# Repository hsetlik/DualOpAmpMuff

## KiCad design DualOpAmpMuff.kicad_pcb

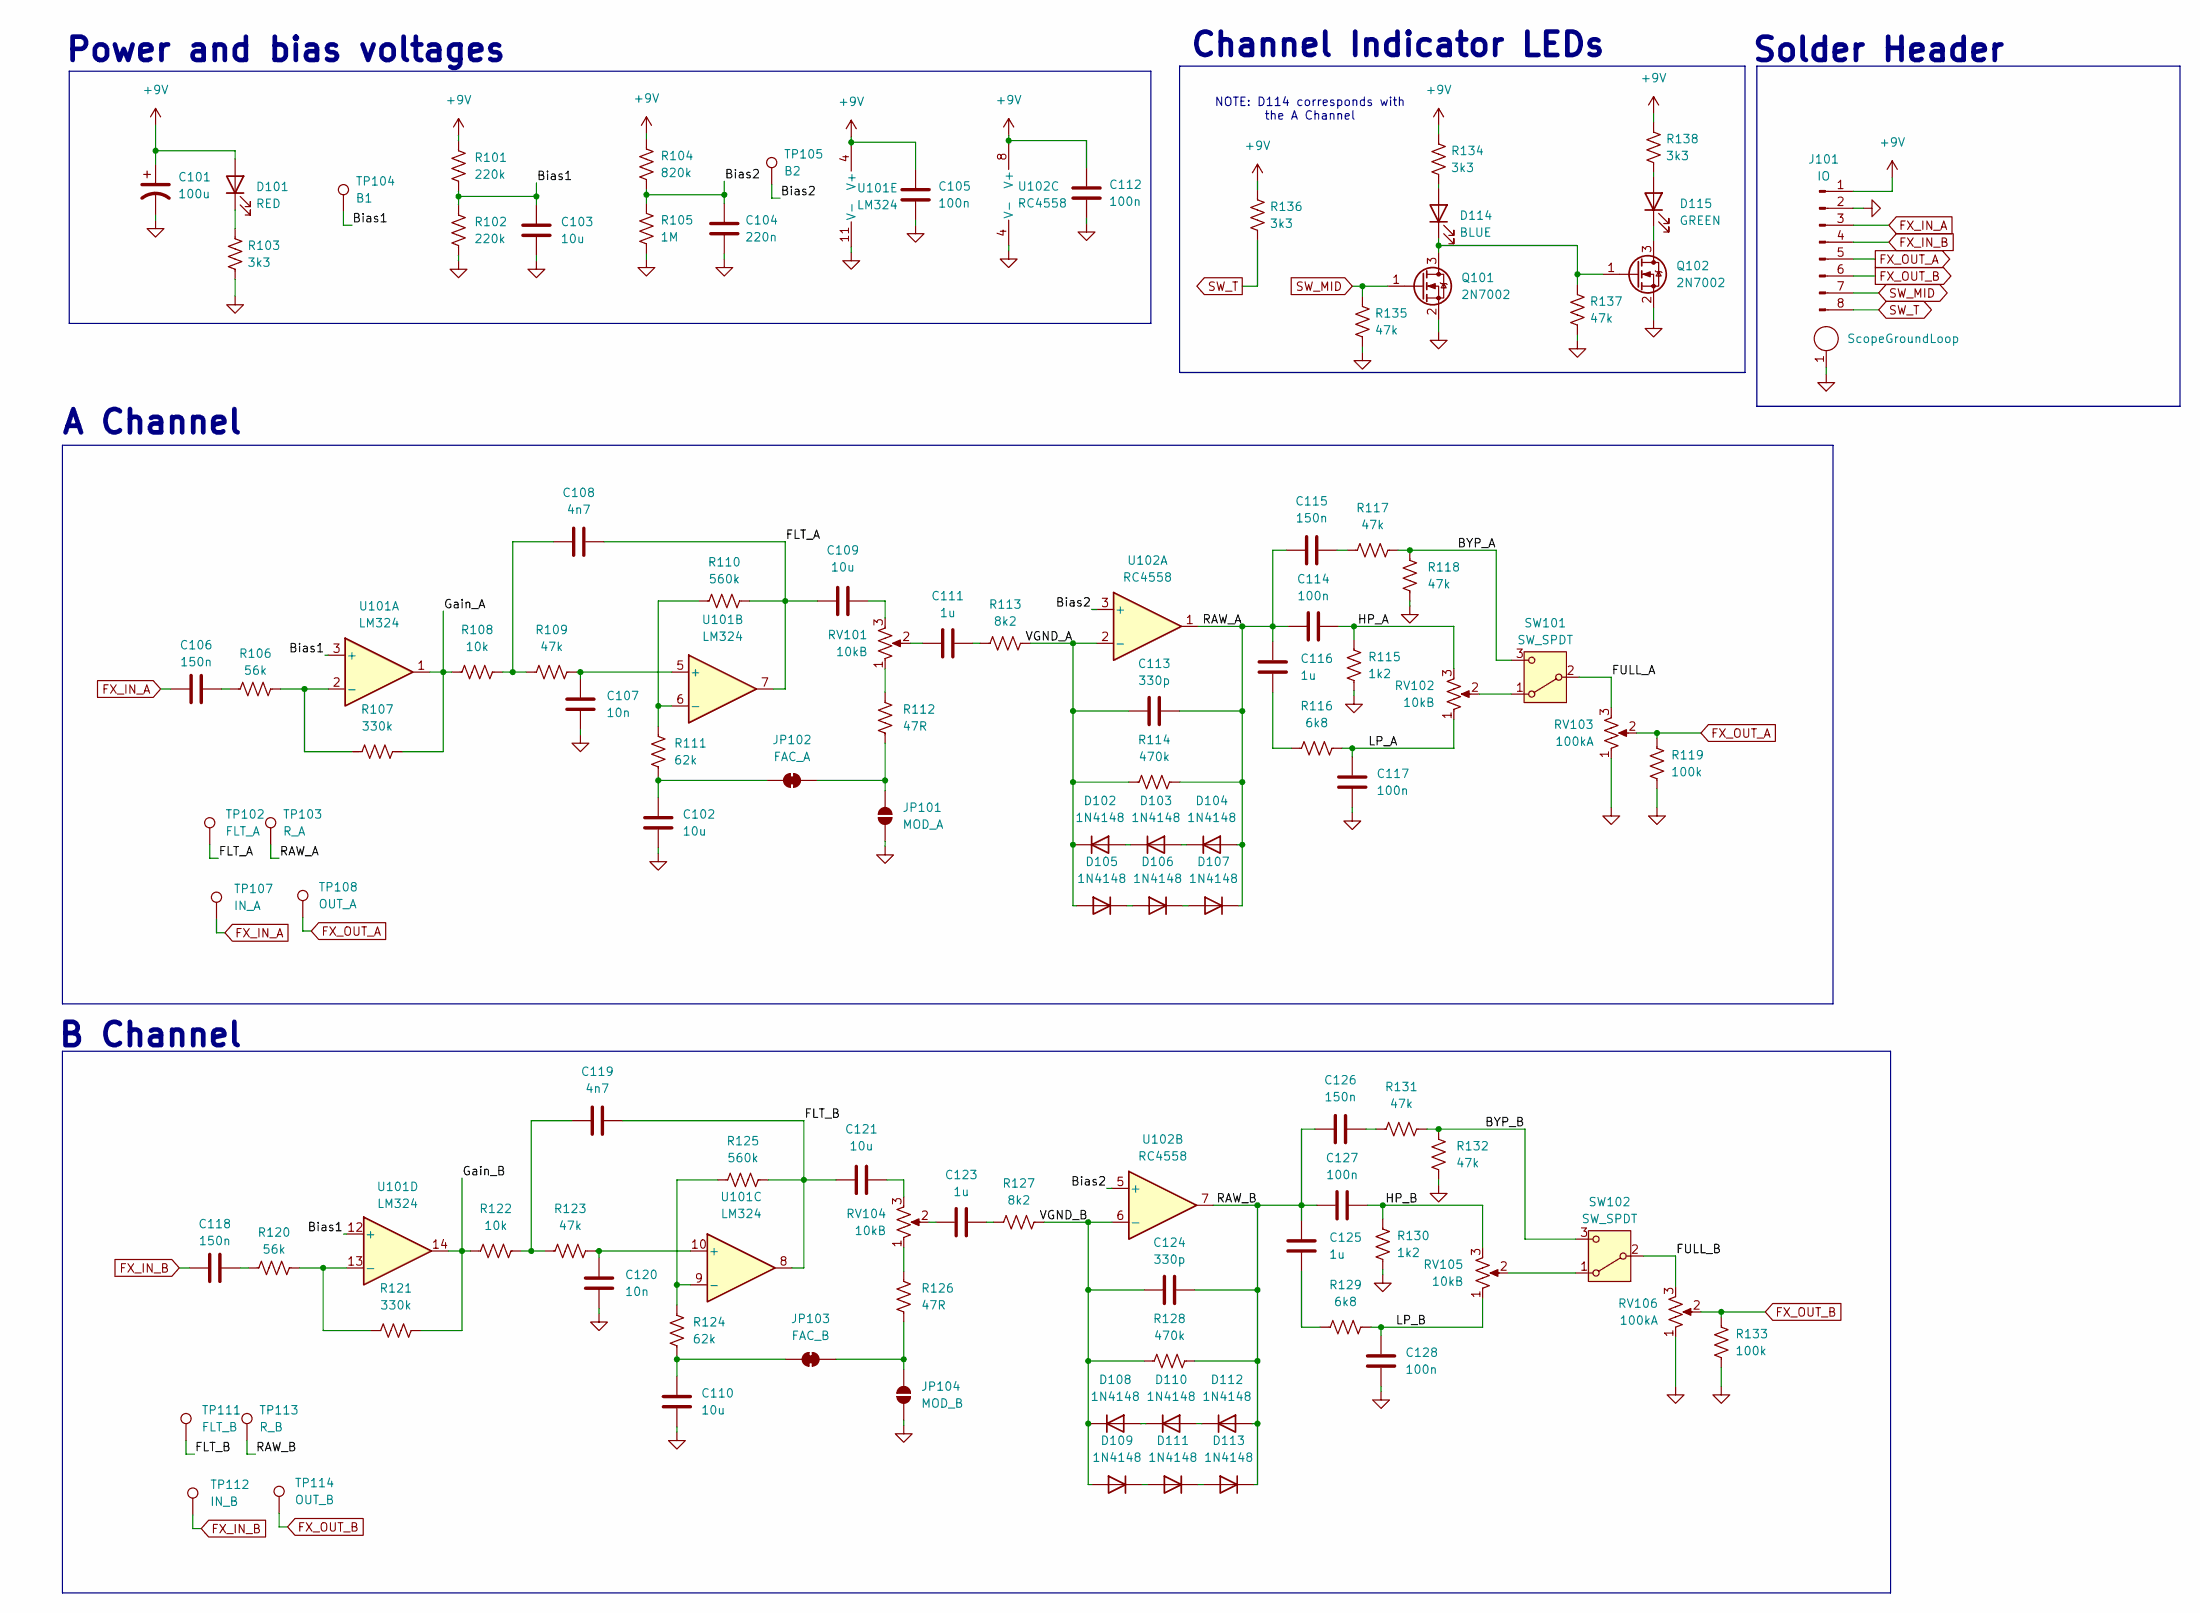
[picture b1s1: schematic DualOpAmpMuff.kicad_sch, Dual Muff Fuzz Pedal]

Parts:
C101: 100u; CP_Radial_D6.3mm_P2.50mm
C102, C103, C109, C110, C121: 10u; C_0805_2012Metric
C104: 220n; C_0805_2012Metric
C105, C112, C114, C117, C127, C128: 100n; C_0805_2012Metric
C106, C115, C118, C126: 150n; C_0805_2012Metric
C107, C120: 10n; C_0805_2012Metric
C108, C119: 4n7; C_0805_2012Metric
C111, C116, C123, C125: 1u; C_0805_2012Metric
C113, C124: 330p; C_0805_2012Metric
D101: RED; LED_D3.0mm
D102, D103, D104, D105, D106, D107, D108, D109, D110, D111, D112, D113: 1N4148; D_SOD-123
D114: BLUE; LED_D3.0mm
D115: GREEN; LED_D3.0mm
J101: IO; PinHeader_1x08_P2.54mm_Vertical
J102: ScopeGroundLoop; THT_GND_WIRE
JP101: MOD_A; SolderJumper-2_P1.3mm_Open_Pad1.0x1.5mm
JP102: FAC_A; SolderJumper-2_P1.3mm_Bridged_Pad1.0x1.5mm
JP103: FAC_B; SolderJumper-2_P1.3mm_Bridged_Pad1.0x1.5mm
JP104: MOD_B; SolderJumper-2_P1.3mm_Open_Pad1.0x1.5mm
Q101, Q102: 2N7002; SOT-23
R101, R102: 220k; R_0805_2012Metric
R103, R134, R136, R138: 3k3; R_0805_2012Metric
R104: 820k; R_0805_2012Metric
R105: 1M; R_0805_2012Metric
R106, R120: 56k; R_0805_2012Metric
R107, R121: 330k; R_0805_2012Metric
R108, R122: 10k; R_0805_2012Metric
R109, R117, R118, R123, R131, R132, R135, R137: 47k; R_0805_2012Metric
R110, R125: 560k; R_0805_2012Metric
R111, R124: 62k; R_0805_2012Metric
R112, R126: 47R; R_0805_2012Metric
R113, R127: 8k2; R_0805_2012Metric
R114, R128: 470k; R_0805_2012Metric
R115, R130: 1k2; R_0805_2012Metric
R116, R129: 6k8; R_0805_2012Metric
R119, R133: 100k; R_0805_2012Metric
RV101, RV102, RV104, RV105: 10kB; Potentiometer_Alpha_RD901F-40-00D_Single_Vertical_CircularH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
RV103, RV106: 100kA; Potentiometer_Alpha_RD901F-40-00D_Single_Vertical_CircularH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
SW101, SW102: SW_SPDT; Switch_Toggle_SPDT_Mini_SolderLug
TP102: FLT_A; TestPoint_THTPad_D2.0mm_Drill1.0mm_VAL
TP103: R_A; TestPoint_THTPad_D2.0mm_Drill1.0mm_VAL
TP104: B1; TestPoint_THTPad_D2.0mm_Drill1.0mm_VAL
TP105: B2; TestPoint_THTPad_D2.0mm_Drill1.0mm_VAL
TP107: IN_A; TestPoint_THTPad_D2.0mm_Drill1.0mm_VAL
TP108: OUT_A; TestPoint_THTPad_D2.0mm_Drill1.0mm_VAL
TP111: FLT_B; TestPoint_THTPad_D2.0mm_Drill1.0mm_VAL
TP112: IN_B; TestPoint_THTPad_D2.0mm_Drill1.0mm_VAL
TP113: R_B; TestPoint_THTPad_D2.0mm_Drill1.0mm_VAL
TP114: OUT_B; TestPoint_THTPad_D2.0mm_Drill1.0mm_VAL
U101: LM324; DIP-14_W7.62mm
U102: RC4558; DIP-8_W7.62mm

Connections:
+9V: C101.1, C105.1, C112.1, D101.2 (A), J101.1, R101.2, R104.2, R134.2, R136.2, R138.2, U101.4 (V+), U102.8 (V+)
/BYP_A: R117.2, R118.1, SW101.3 (C)
/BYP_B: R131.2, R132.1, SW102.3 (C)
/Bias1: C103.1, R101.1, R102.2, TP104.1, U101.3 (+), U101.12 (+)
/Bias2: C104.1, R104.1, R105.2, TP105.1, U102.3 (+), U102.5 (+)
/FLT_A: C108.2, C109.2, R110.2, TP102.1, U101.7
/FLT_B: C119.2, C121.1, R125.2, TP111.1, U101.8
/FULL_A: RV103.3, SW101.2 (B)
/FULL_B: RV106.3, SW102.2 (B)
/Gain_A: R107.2, R108.1, U101.1
/Gain_B: R121.2, R122.1, U101.14
/HP_A: C114.2, R115.1, RV102.3
/HP_B: C127.2, R130.1, RV105.3
/LP_A: C117.1, R116.2, RV102.1
/LP_B: C128.1, R129.2, RV105.1
/RAW_A: C113.2, C114.1, C115.1, C116.1, D104.2 (A), D107.1 (K), R114.2, TP103.1, U102.1
/RAW_B: C124.2, C125.1, C126.1, C127.1, D112.2 (A), D113.1 (K), R128.2, TP113.1, U102.7
/VGND_A: C113.1, D102.1 (K), D105.2 (A), R113.2, R114.1, U102.2 (-)
/VGND_B: C124.1, D108.1 (K), D109.2 (A), R127.2, R128.1, U102.6 (-)
FX_IN_A: C106.2, J101.3, TP107.1
FX_IN_B: C118.2, J101.4, TP112.1
FX_OUT_A: J101.5, R119.1, RV103.2, TP108.1
FX_OUT_B: J101.6, R133.1, RV106.2, TP114.1
GND: C101.2, C102.2, C103.2, C104.2, C105.2, C107.2, C110.2, C112.2, C117.2, C120.2, C128.2, J101.2, J102.1, JP101.1 (A), JP104.1 (A), Q101.2 (S), Q102.2 (S), R102.1, R103.1, R105.1, R115.2, R118.2, R119.2, R130.2, R132.2, R133.2, R135.1, R137.1, RV103.1, RV106.1, U101.11 (V-), U102.4 (V-)
unnamed: C106.1, R106.1
unnamed: C108.1, R108.2, R109.1
unnamed: C109.1, RV101.3
unnamed: C111.1, RV101.2
unnamed: C111.2, R113.1
unnamed: C115.2, R117.1
unnamed: C116.2, R116.1
unnamed: C118.1, R120.1
unnamed: C119.1, R122.2, R123.1
unnamed: C121.2, RV104.3
unnamed: C123.1, RV104.2
unnamed: C123.2, R127.1
unnamed: C125.2, R129.1
unnamed: C126.2, R131.1
unnamed: D101.1 (K), R103.2
unnamed: D102.2 (A), D103.1 (K)
unnamed: D103.2 (A), D104.1 (K)
unnamed: D105.1 (K), D106.2 (A)
unnamed: D106.1 (K), D107.2 (A)
unnamed: D108.2 (A), D110.1 (K)
unnamed: D109.1 (K), D111.2 (A)
unnamed: D110.2 (A), D112.1 (K)
unnamed: D111.1 (K), D113.2 (A)
unnamed: D114.2 (A), R134.1
unnamed: D114.1 (K), Q101.3 (D), Q102.1 (G), R137.2
unnamed: D115.2 (A), R138.1
unnamed: D115.1 (K), Q102.3 (D)
unnamed: JP101.2 (B), JP102.2 (B), R112.2
unnamed: C102.1, JP102.1 (A), R111.2
unnamed: C110.1, JP103.1 (A), R124.2
unnamed: JP103.2 (B), JP104.2 (B), R126.2
unnamed: R112.1, RV101.1
unnamed: R126.1, RV104.1
unnamed: RV102.2, SW101.1 (A)
unnamed: RV105.2, SW102.1 (A)
unnamed: R106.2, R107.1, U101.2 (-)
unnamed: C107.1, R109.2, U101.5 (+)
unnamed: R110.1, R111.1, U101.6 (-)
unnamed: C120.1, R123.2, U101.10 (+)
unnamed: R124.1, R125.1, U101.9 (-)
unnamed: R120.2, R121.1, U101.13 (-)
SW_MID: J101.7, Q101.1 (G), R135.2
SW_T: J101.8, R136.1

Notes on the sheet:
Solder Header
NOTE: D114 corresponds with the A Channel
Power and bias voltages
Channel Indicator LEDs
A Channel
B Channel

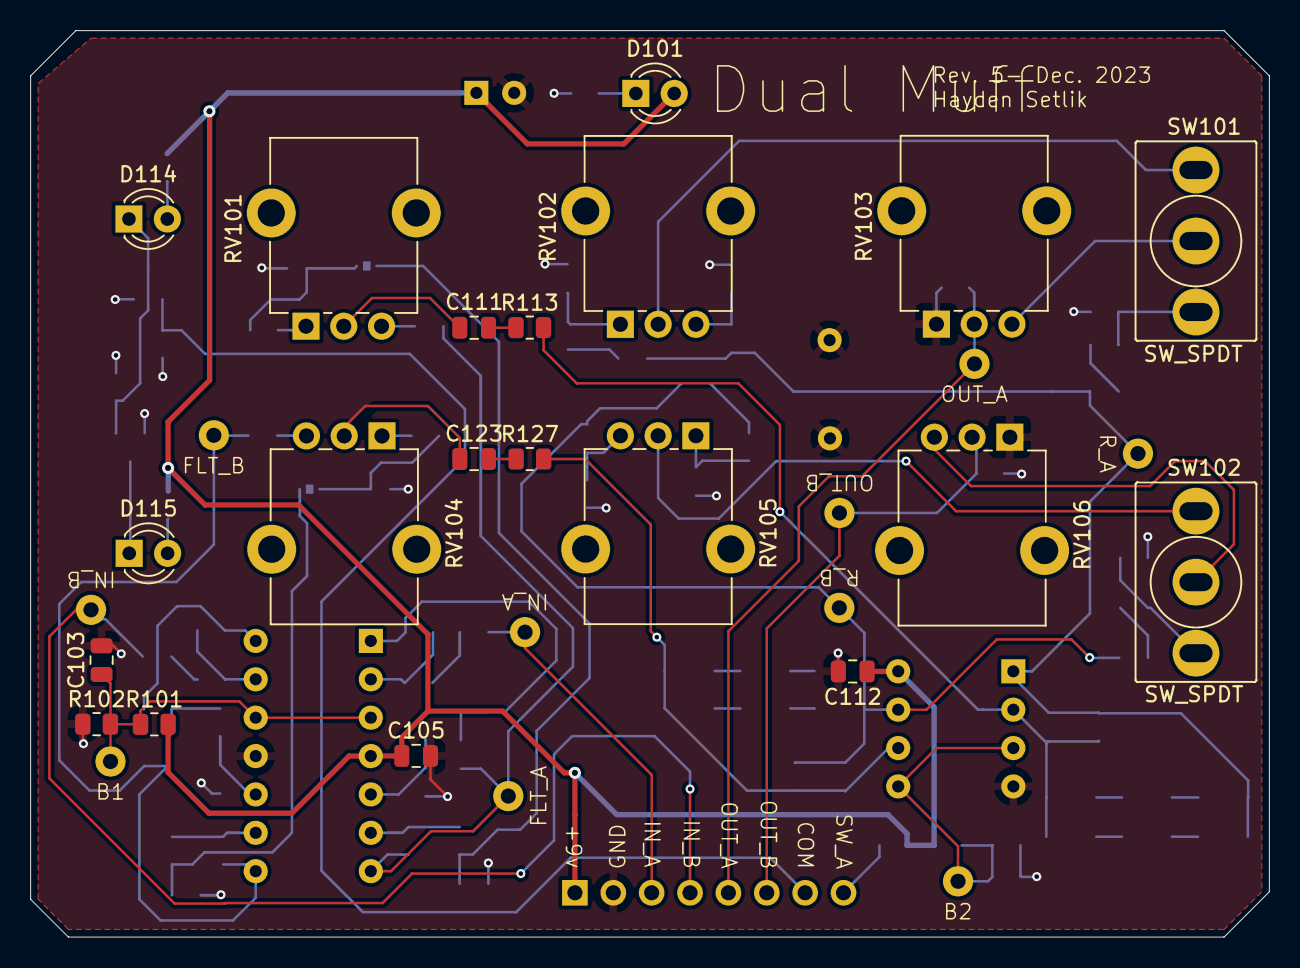
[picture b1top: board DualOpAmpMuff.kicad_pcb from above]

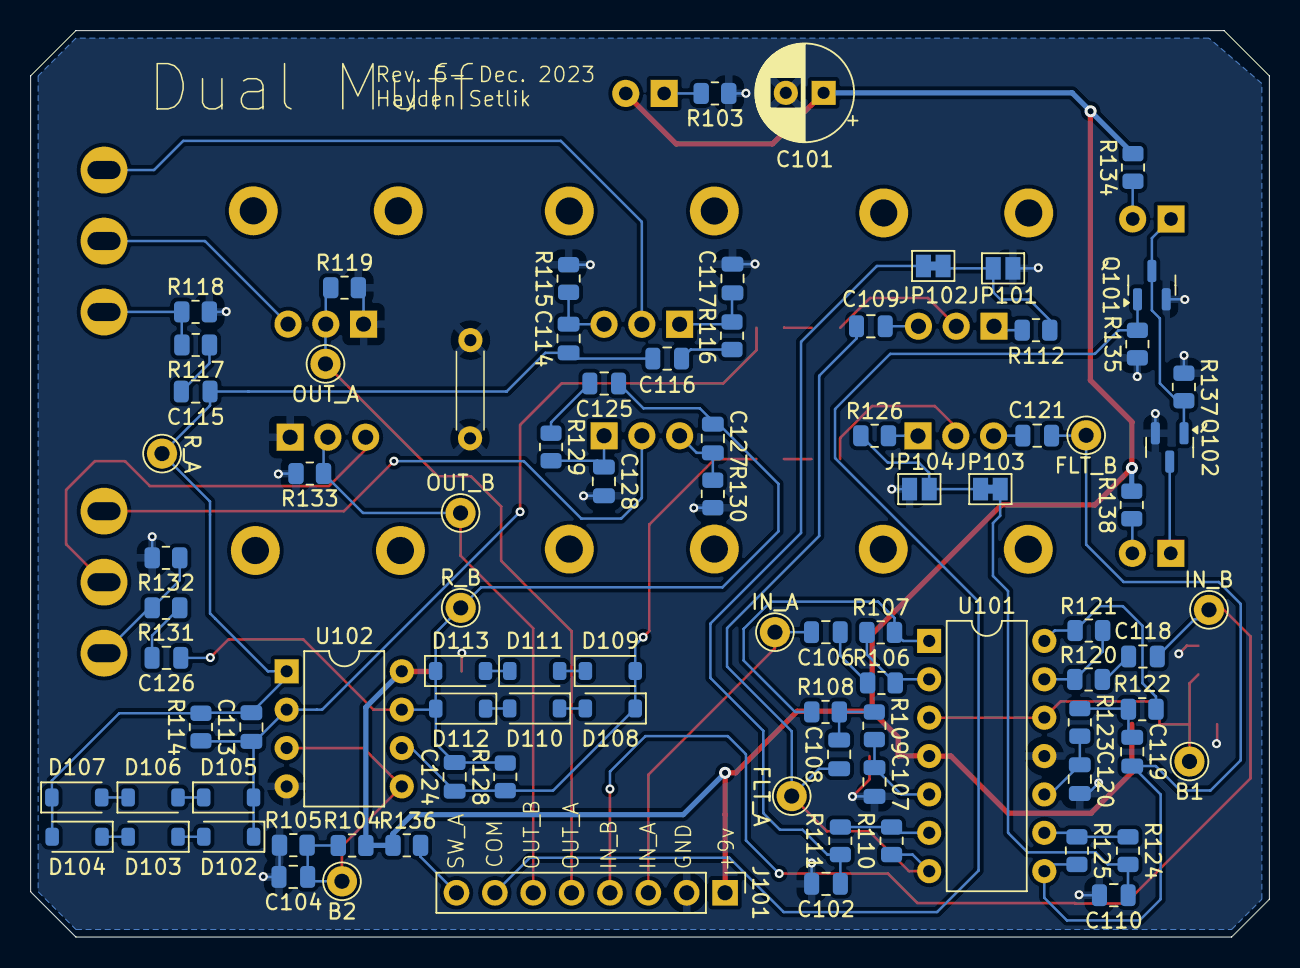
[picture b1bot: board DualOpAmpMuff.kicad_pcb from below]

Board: 2 copper layers, 82.0 x 60.0 mm, 108 parts (88 on the bottom side), 67 nets.

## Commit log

2024-12-21 switched to 2 layer
2024-12-22 smaller outline laid out
2024-12-22 preliminary routing
2024-12-22 DRC passing on 2 layer
2024-12-22 silkscreen done, routing cleaned up
